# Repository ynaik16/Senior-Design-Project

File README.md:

# Senior-Design-Project
Custom Designed PCB capable of running Linux, that monitors the level of hazardous gases in the immediate environment.

This is my Senior Design Project developed by a team of 3 at California State University, East Bay. It is based on Olimex's "OLINUXINO" Linux based PCB.

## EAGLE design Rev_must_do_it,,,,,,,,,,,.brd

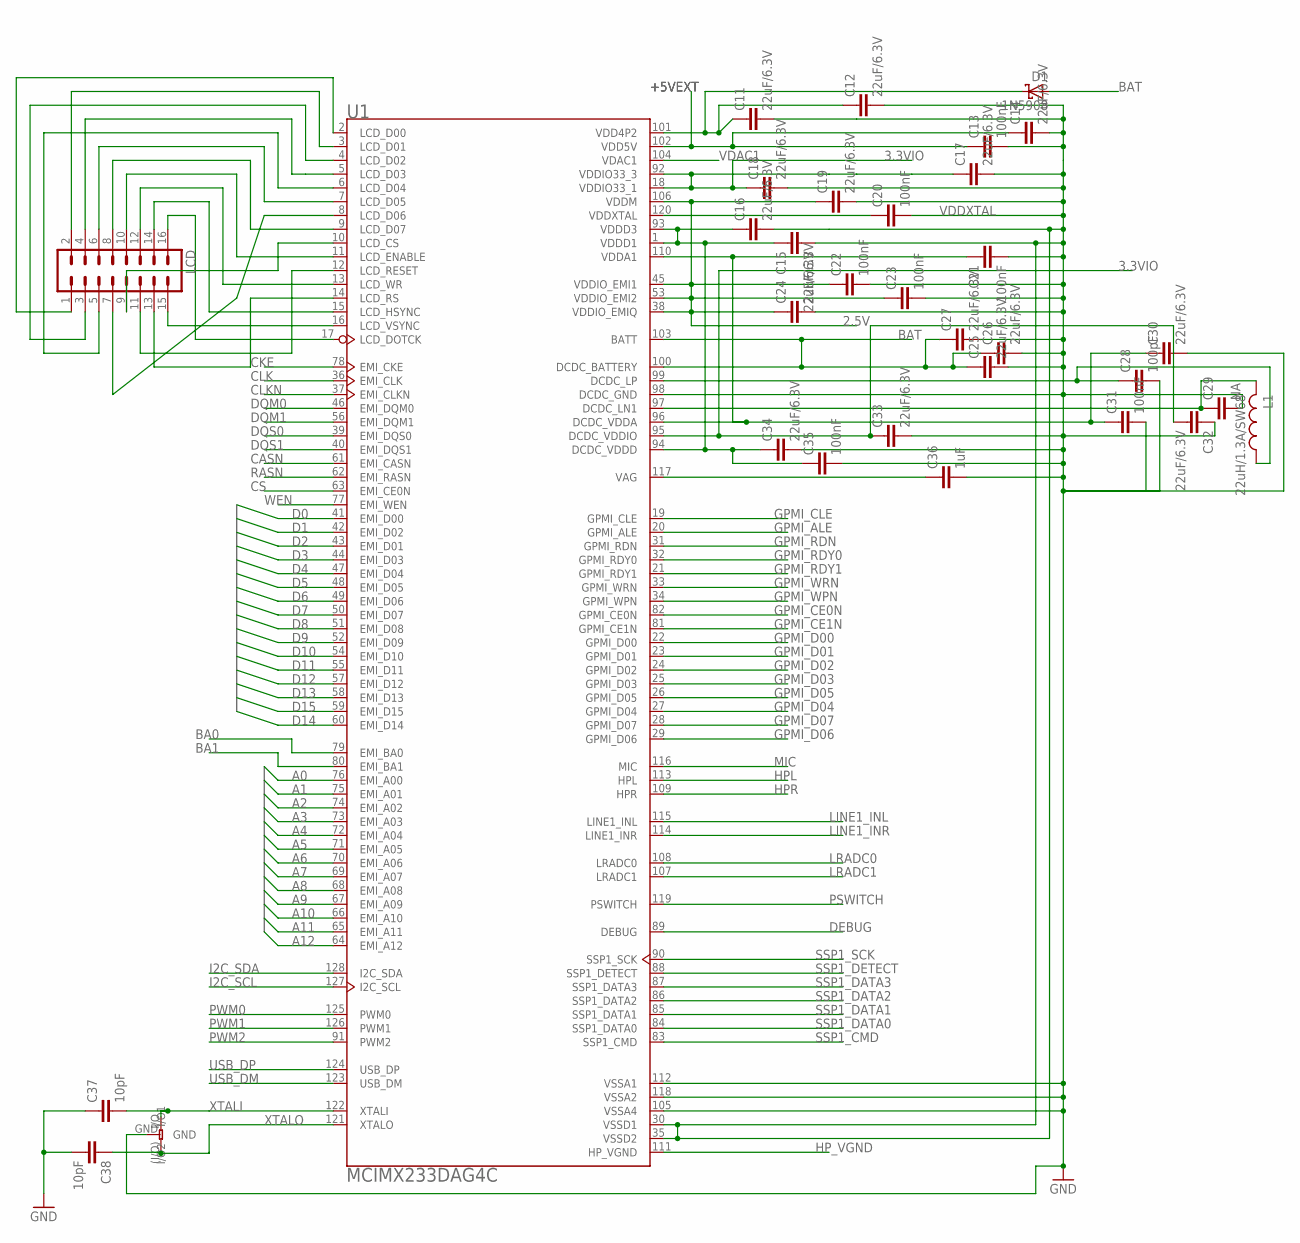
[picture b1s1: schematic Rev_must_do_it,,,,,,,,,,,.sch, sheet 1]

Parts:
C11, C12, C14, C15, C16, C17, C18, C19, C24, C25, C26, C27, C30, C32, C33, C34: 22uF/6.3V; C1206
C13, C20, C21, C22, C23, C31, C35: 100nF; C1206
C28: 100pF; C1206
C29: NA; C1206
C36: 1uF; C1206
C37, C38: 10pF; C1206
D1: 1N5908; C4111-15
L1: 22uH/1.3A/SW68; LAL02
LCD: MA08-2
U1: MCIMX233DAG4C; QFP40P1600X1600X160-128N
U$2: CRYSTAL

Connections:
2.5V: C19.1, C22.1, C23.1, C24.1, U1.38 (VDDIO_EMIQ), U1.45 (VDDIO_EMI1), U1.53 (VDDIO_EMI2), U1.106 (VDDM); also elsewhere on the board
3.3VIO: C17.1, C18.1, C32.2, C33.1, U1.18 (VDDIO33_1), U1.92 (VDDIO33_3), U1.95 (DCDC_VDDIO); also elsewhere on the board
+5VEXT: C13.1, C14.1, U1.102 (VDD5V); also elsewhere on the board
A0: U1.76 (EMI_A00); also elsewhere on the board
A1: U1.75 (EMI_A01); also elsewhere on the board
A2: U1.74 (EMI_A02); also elsewhere on the board
A3: U1.73 (EMI_A03); also elsewhere on the board
A4: U1.72 (EMI_A04); also elsewhere on the board
A5: U1.71 (EMI_A05); also elsewhere on the board
A6: U1.70 (EMI_A06); also elsewhere on the board
A7: U1.69 (EMI_A07); also elsewhere on the board
A8: U1.68 (EMI_A08); also elsewhere on the board
A9: U1.67 (EMI_A09); also elsewhere on the board
A10: U1.66 (EMI_A10); also elsewhere on the board
A11: U1.65 (EMI_A11); also elsewhere on the board
A12: U1.64 (EMI_A12); also elsewhere on the board
BA0: U1.79 (EMI_BA0); also elsewhere on the board
BA1: U1.80 (EMI_BA1); also elsewhere on the board
BAT: C25.1, C26.1, C27.1, D1.A, U1.100 (DCDC_BATTERY), U1.103 (BATT)
CASN: U1.61 (EMI_CASN); also elsewhere on the board
CKE: U1.78 (EMI_CKE); also elsewhere on the board
CLK: U1.36 (EMI_CLK); also elsewhere on the board
CLKN: U1.37 (EMI_CLKN); also elsewhere on the board
CS: U1.63 (EMI_CE0N); also elsewhere on the board
D0: U1.41 (EMI_D00); also elsewhere on the board
D1: U1.42 (EMI_D02); also elsewhere on the board
D2: U1.43 (EMI_D01); also elsewhere on the board
D3: U1.44 (EMI_D03); also elsewhere on the board
D4: U1.47 (EMI_D04); also elsewhere on the board
D5: U1.48 (EMI_D05); also elsewhere on the board
D6: U1.49 (EMI_D06); also elsewhere on the board
D7: U1.50 (EMI_D07); also elsewhere on the board
D8: U1.51 (EMI_D08); also elsewhere on the board
D9: U1.52 (EMI_D09); also elsewhere on the board
D10: U1.54 (EMI_D10); also elsewhere on the board
D11: U1.55 (EMI_D11); also elsewhere on the board
D12: U1.57 (EMI_D12); also elsewhere on the board
D13: U1.58 (EMI_D13); also elsewhere on the board
D14: U1.60 (EMI_D14)
D15: U1.59 (EMI_D15); also elsewhere on the board
DCDC_VDDA1: C21.1, C30.1, C31.1, U1.96 (DCDC_VDDA), U1.110 (VDDA1)
DCDC_VDDD: C15.1, C16.1, C34.1, C35.1, U1.1 (VDDD1), U1.93 (VDDD3), U1.94 (DCDC_VDDD)
DEBUG: U1.89 (DEBUG); also elsewhere on the board
DQM0: U1.46 (EMI_DQM0); also elsewhere on the board
DQM1: U1.56 (EMI_DQM1); also elsewhere on the board
DQS0: U1.39 (EMI_DQS0); also elsewhere on the board
DQS1: U1.40 (EMI_DQS1); also elsewhere on the board
GND: C11.2, C12.2, C13.2, C14.2, C15.2, C16.2, C17.2, C18.2, C19.2, C20.2, C21.2, C22.2, C23.2, C24.2, C25.2, C26.2, C27.2, C28.2, C29.2, C30.2, C31.2, C32.1, C33.2, C34.2, C35.2, C36.2, C37.1, C38.2, U1.30 (VSSD1), U1.35 (VSSD2), U1.98 (DCDC_GND), U1.105 (VSSA4), U1.112 (VSSA1), U1.118 (VSSA2), U$2.GND; also elsewhere on the board
GPMI_ALE: U1.20 (GPMI_ALE); also elsewhere on the board
GPMI_CE0N: U1.82 (GPMI_CE0N); also elsewhere on the board
GPMI_CE1N: U1.81 (GPMI_CE1N); also elsewhere on the board
GPMI_CLE: U1.19 (GPMI_CLE); also elsewhere on the board
GPMI_D00: U1.22 (GPMI_D00); also elsewhere on the board
GPMI_D01: U1.23 (GPMI_D01); also elsewhere on the board
GPMI_D02: U1.24 (GPMI_D02); also elsewhere on the board
GPMI_D03: U1.25 (GPMI_D03); also elsewhere on the board
GPMI_D04: U1.27 (GPMI_D04); also elsewhere on the board
GPMI_D05: U1.26 (GPMI_D05); also elsewhere on the board
GPMI_D06: U1.29 (GPMI_D06); also elsewhere on the board
GPMI_D07: U1.28 (GPMI_D07); also elsewhere on the board
GPMI_RDN: U1.31 (GPMI_RDN); also elsewhere on the board
GPMI_RDY0: U1.32 (GPMI_RDY0); also elsewhere on the board
GPMI_RDY1: U1.21 (GPMI_RDY1); also elsewhere on the board
GPMI_WPN: U1.34 (GPMI_WPN); also elsewhere on the board
GPMI_WRN: U1.33 (GPMI_WRN); also elsewhere on the board
HPL: U1.113 (HPL); also elsewhere on the board
HPR: U1.109 (HPR); also elsewhere on the board
HP_VGND: U1.111 (HP_VGND)
I2C_SCL: U1.127 (I2C_SCL); also elsewhere on the board
I2C_SDA: U1.128 (I2C_SDA); also elsewhere on the board
LINE1_INL: U1.115 (LINE1_INL); also elsewhere on the board
LINE1_INR: U1.114 (LINE1_INR); also elsewhere on the board
LRADC0: U1.108 (LRADC0); also elsewhere on the board
LRADC1: U1.107 (LRADC1); also elsewhere on the board
MIC: U1.116 (MIC); also elsewhere on the board
unnamed: C36.1, U1.117 (VAG)
unnamed: C11.1, C12.1, D1.C, U1.101 (VDD4P2)
unnamed: LCD.1, U1.2 (LCD_D00)
unnamed: C29.1, L1.2, U1.97 (DCDC_LN1)
unnamed: C28.1, L1.1, U1.99 (DCDC_LP)
unnamed: LCD.2, U1.3 (LCD_D01)
unnamed: LCD.3, U1.4 (LCD_D02)
unnamed: LCD.4, U1.5 (LCD_D03)
unnamed: LCD.5, U1.6 (LCD_D04)
unnamed: LCD.6, U1.7 (LCD_D05)
unnamed: LCD.7, U1.8 (LCD_D06)
unnamed: LCD.8, U1.9 (LCD_D07)
unnamed: LCD.9, U1.10 (LCD_CS)
unnamed: LCD.10, U1.11 (LCD_ENABLE)
unnamed: LCD.11, U1.12 (LCD_RESET)
unnamed: LCD.12, U1.13 (LCD_WR)
unnamed: LCD.13, U1.14 (LCD_RS)
unnamed: LCD.14, U1.15 (LCD_HSYNC)
unnamed: LCD.15, U1.16 (LCD_VSYNC)
unnamed: LCD.16, U1.17 (LCD_DOTCK)
PSWITCH: U1.119 (PSWITCH); also elsewhere on the board
PWM0: U1.125 (PWM0); also elsewhere on the board
PWM1: U1.126 (PWM1); also elsewhere on the board
PWM2: U1.91 (PWM2); also elsewhere on the board
RASN: U1.62 (EMI_RASN); also elsewhere on the board
SSP1_CMD: U1.83 (SSP1_CMD); also elsewhere on the board
SSP1_DATA0: U1.84 (SSP1_DATA0); also elsewhere on the board
SSP1_DATA1: U1.85 (SSP1_DATA1); also elsewhere on the board
SSP1_DATA2: U1.86 (SSP1_DATA2); also elsewhere on the board
SSP1_DATA3: U1.87 (SSP1_DATA3); also elsewhere on the board
SSP1_DETECT: U1.88 (SSP1_DETECT); also elsewhere on the board
SSP1_SCK: U1.90 (SSP1_SCK); also elsewhere on the board
USB_DM: U1.123 (USB_DM); also elsewhere on the board
USB_DP: U1.124 (USB_DP); also elsewhere on the board
VDAC1: U1.104 (VDAC1)
VDDXTAL: C20.1, U1.120 (VDDXTAL); also elsewhere on the board
WEN: U1.77 (EMI_WEN); also elsewhere on the board
XTALI: C37.2, U1.122 (XTALI), U$2.I/O (I/O2); also elsewhere on the board
XTALO: C38.1, U1.121 (XTALO), U$2.(I/O) (I/O1); also elsewhere on the board

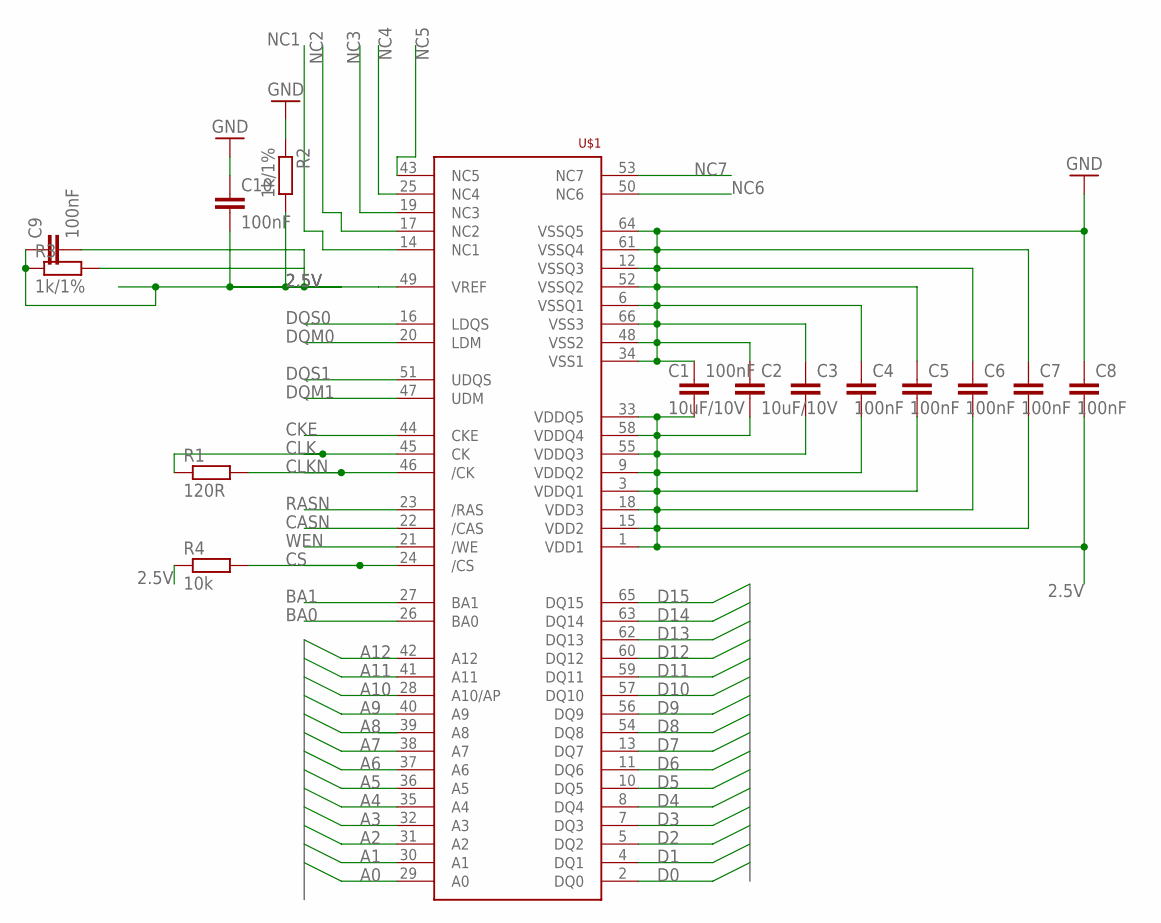
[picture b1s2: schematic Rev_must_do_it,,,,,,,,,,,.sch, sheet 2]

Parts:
C1, C3: 10uF/10V; C1206
C2, C4, C5, C6, C7, C8, C9, C10: 100nF; C1206
R1: 120R; R1206
R2, R3: 1k/1%; R1206
R4: 10k; R1206
U$1: HY5DU121622D(L)T(P)-JTSOP-II; TSOP66

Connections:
2.5V: C1.2, C2.2, C3.2, C4.2, C5.2, C6.2, C7.2, C8.2, C9.1, C9.2, C10.2, R2.2, R3.1, R4.1, U$1.1 (VDD1), U$1.3 (VDDQ1), U$1.9 (VDDQ2), U$1.15 (VDD2), U$1.18 (VDD3), U$1.33 (VDDQ5), U$1.49 (VREF), U$1.55 (VDDQ3), U$1.58 (VDDQ4); also elsewhere on the board
A0: U$1.29 (A0); also elsewhere on the board
A1: U$1.30 (A1); also elsewhere on the board
A2: U$1.31 (A2); also elsewhere on the board
A3: U$1.32 (A3); also elsewhere on the board
A4: U$1.35 (A4); also elsewhere on the board
A5: U$1.36 (A5); also elsewhere on the board
A6: U$1.37 (A6); also elsewhere on the board
A7: U$1.38 (A7); also elsewhere on the board
A8: U$1.39 (A8); also elsewhere on the board
A9: U$1.40 (A9), U$1.63 (DQ14); also elsewhere on the board
A10: U$1.28 (A10/AP); also elsewhere on the board
A11: U$1.41 (A11); also elsewhere on the board
A12: U$1.42 (A12); also elsewhere on the board
BA0: U$1.26 (BA0); also elsewhere on the board
BA1: U$1.27 (BA1); also elsewhere on the board
CASN: U$1.22 (/CAS); also elsewhere on the board
CKE: U$1.44 (CKE); also elsewhere on the board
CLK: R1.1, U$1.45 (CK); also elsewhere on the board
CLKN: R1.2, U$1.46 (/CK); also elsewhere on the board
CS: R4.2, U$1.24 (/CS); also elsewhere on the board
D0: U$1.2 (DQ0); also elsewhere on the board
D1: U$1.4 (DQ1); also elsewhere on the board
D2: U$1.5 (DQ2); also elsewhere on the board
D3: U$1.7 (DQ3); also elsewhere on the board
D4: U$1.8 (DQ4); also elsewhere on the board
D5: U$1.10 (DQ5); also elsewhere on the board
D6: U$1.11 (DQ6); also elsewhere on the board
D7: U$1.13 (DQ7); also elsewhere on the board
D8: U$1.54 (DQ8); also elsewhere on the board
D9: U$1.56 (DQ9); also elsewhere on the board
D10: U$1.57 (DQ10); also elsewhere on the board
D11: U$1.59 (DQ11); also elsewhere on the board
D12: U$1.60 (DQ12); also elsewhere on the board
D13: U$1.62 (DQ13); also elsewhere on the board
D15: U$1.65 (DQ15); also elsewhere on the board
DQM0: U$1.20 (LDM); also elsewhere on the board
DQM1: U$1.47 (UDM); also elsewhere on the board
DQS0: U$1.16 (LDQS); also elsewhere on the board
DQS1: U$1.51 (UDQS); also elsewhere on the board
GND: C1.1, C2.1, C3.1, C4.1, C5.1, C6.1, C7.1, C8.1, C10.1, R2.1, U$1.6 (VSSQ1), U$1.12 (VSSQ3), U$1.34 (VSS1), U$1.48 (VSS2), U$1.52 (VSSQ2), U$1.61 (VSSQ4), U$1.64 (VSSQ5), U$1.66 (VSS3); also elsewhere on the board
NC1: U$1.14 (NC1); also elsewhere on the board
NC2: U$1.17 (NC2); also elsewhere on the board
NC3: U$1.19 (NC3); also elsewhere on the board
NC4: U$1.25 (NC4); also elsewhere on the board
NC5: U$1.43 (NC5); also elsewhere on the board
NC6: U$1.50 (NC6); also elsewhere on the board
NC7: U$1.53 (NC7); also elsewhere on the board
RASN: U$1.23 (/RAS); also elsewhere on the board
WEN: U$1.21 (/WE); also elsewhere on the board

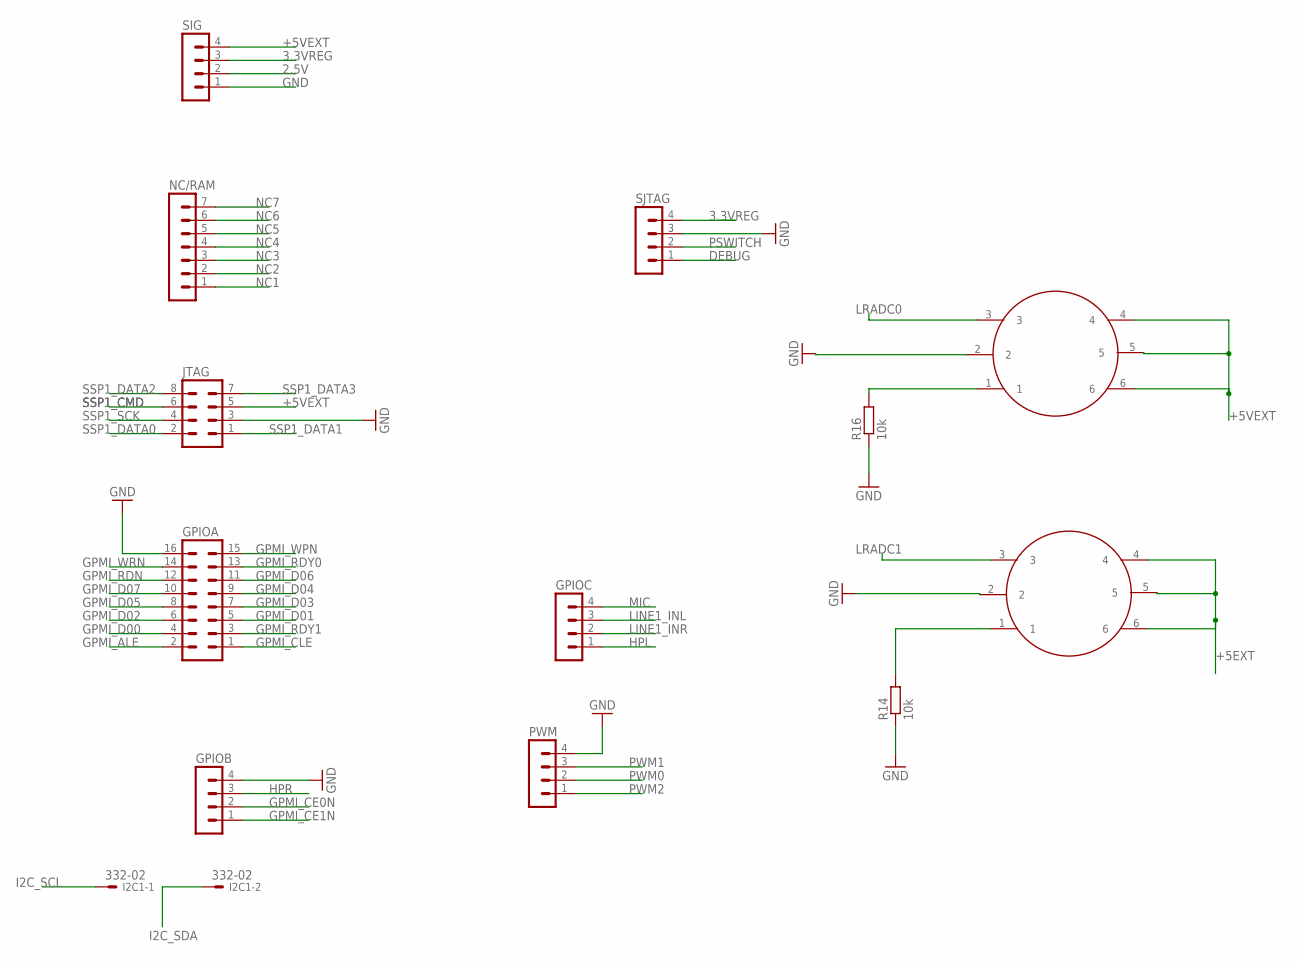
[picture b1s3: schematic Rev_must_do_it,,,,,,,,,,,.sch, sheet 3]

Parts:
GPIOA: MA08-2
GPIOB: MA04-1
GPIOC: MA04-1
I2C1: 332-02
JTAG: MA04-2
NC/RAM: MA07-1
PWM: MA04-1
R14, R16: 10k; R1206
SIG: MA04-1
SJTAG: MA04-1
U$5, U$6: SENSOR

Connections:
2.5V: SIG.2; also elsewhere on the board
3.3VREG: SIG.3, SJTAG.4; also elsewhere on the board
+5EXT: U$6.4, U$6.5, U$6.6
+5VEXT: JTAG.5, SIG.4, U$5.4, U$5.5, U$5.6; also elsewhere on the board
DEBUG: SJTAG.1; also elsewhere on the board
GND: GPIOA.16, GPIOB.4, JTAG.3, PWM.4, R14.1, R16.1, SIG.1, SJTAG.3, U$5.2, U$6.2; also elsewhere on the board
GPMI_ALE: GPIOA.2; also elsewhere on the board
GPMI_CE0N: GPIOB.2; also elsewhere on the board
GPMI_CE1N: GPIOB.1; also elsewhere on the board
GPMI_CLE: GPIOA.1; also elsewhere on the board
GPMI_D00: GPIOA.4; also elsewhere on the board
GPMI_D01: GPIOA.5; also elsewhere on the board
GPMI_D02: GPIOA.6; also elsewhere on the board
GPMI_D03: GPIOA.7; also elsewhere on the board
GPMI_D04: GPIOA.9; also elsewhere on the board
GPMI_D05: GPIOA.8; also elsewhere on the board
GPMI_D06: GPIOA.11; also elsewhere on the board
GPMI_D07: GPIOA.10; also elsewhere on the board
GPMI_RDN: GPIOA.12; also elsewhere on the board
GPMI_RDY0: GPIOA.13; also elsewhere on the board
GPMI_RDY1: GPIOA.3; also elsewhere on the board
GPMI_WPN: GPIOA.15; also elsewhere on the board
GPMI_WRN: GPIOA.14; also elsewhere on the board
HPL: GPIOC.1; also elsewhere on the board
HPR: GPIOB.3; also elsewhere on the board
I2C_SCL: I2C1.1; also elsewhere on the board
I2C_SDA: I2C1.2; also elsewhere on the board
LINE1_INL: GPIOC.3; also elsewhere on the board
LINE1_INR: GPIOC.2; also elsewhere on the board
LRADC0: U$5.3; also elsewhere on the board
LRADC1: U$6.3; also elsewhere on the board
MIC: GPIOC.4; also elsewhere on the board
unnamed: R16.2, U$5.1
unnamed: R14.2, U$6.1
NC1: NC/RAM.1; also elsewhere on the board
NC2: NC/RAM.2; also elsewhere on the board
NC3: NC/RAM.3; also elsewhere on the board
NC4: NC/RAM.4; also elsewhere on the board
NC5: NC/RAM.5; also elsewhere on the board
NC6: NC/RAM.6; also elsewhere on the board
NC7: NC/RAM.7; also elsewhere on the board
PSWITCH: SJTAG.2; also elsewhere on the board
PWM0: PWM.2; also elsewhere on the board
PWM1: PWM.3; also elsewhere on the board
PWM2: PWM.1; also elsewhere on the board
SSP1_CMD: JTAG.6; also elsewhere on the board
SSP1_DATA0: JTAG.2; also elsewhere on the board
SSP1_DATA1: JTAG.1; also elsewhere on the board
SSP1_DATA2: JTAG.8; also elsewhere on the board
SSP1_DATA3: JTAG.7; also elsewhere on the board
SSP1_SCK: JTAG.4; also elsewhere on the board

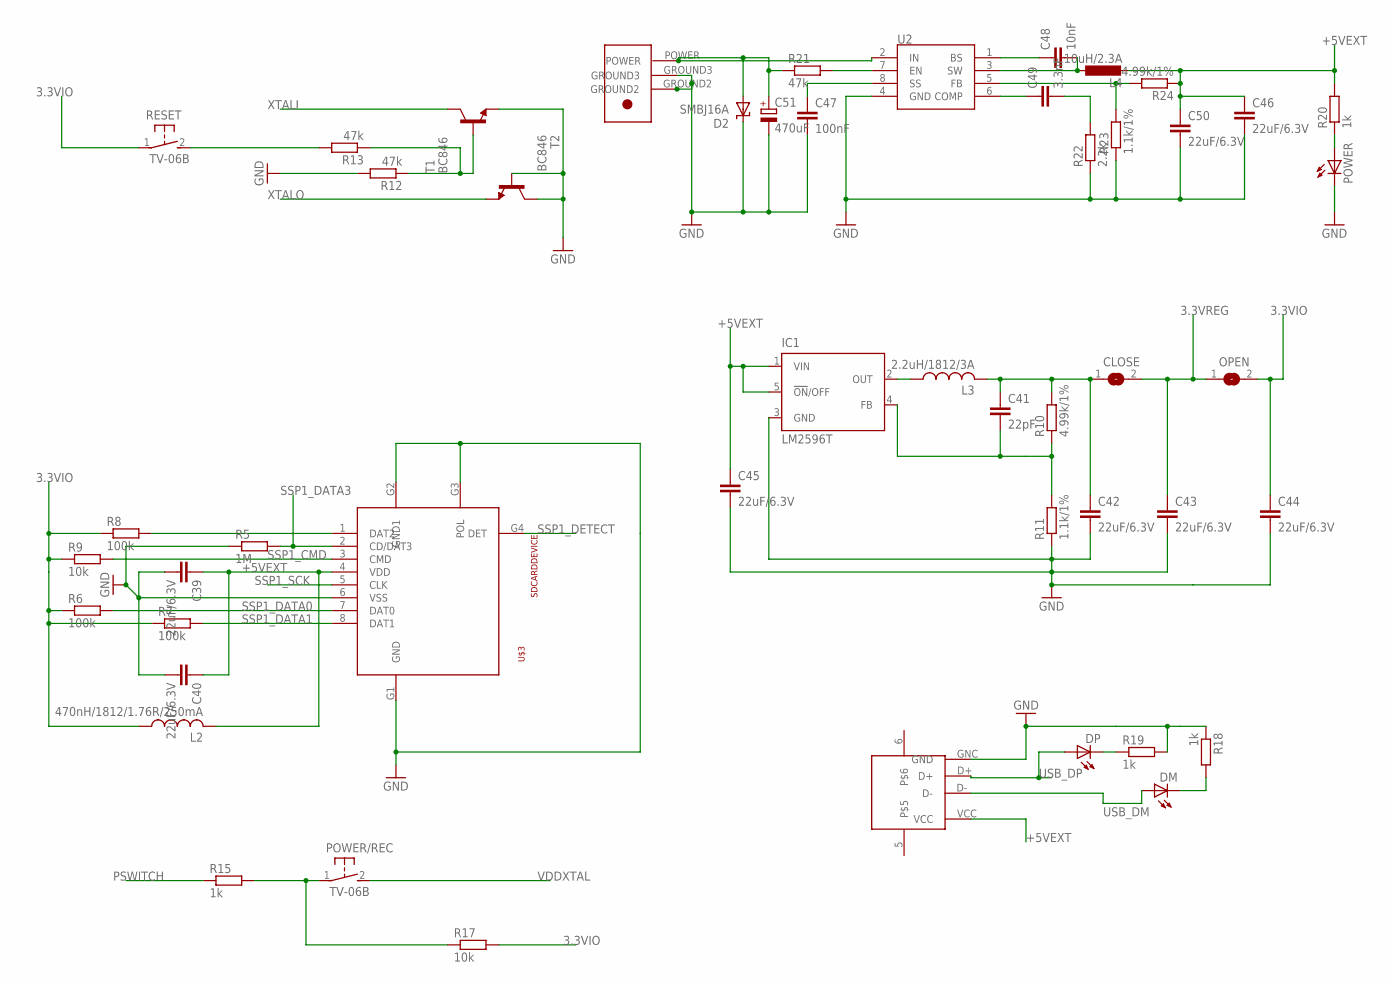
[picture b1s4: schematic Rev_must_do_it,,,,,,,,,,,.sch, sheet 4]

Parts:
C39, C40, C42, C43, C44, C45, C46, C50: 22uF/6.3V; C1206
C41: 22pF; C1206
C47: 100nF; C1206
C48: 10nF; C1206
C49: 3.3nF; C1206
C51: 470uF; 085CS_1AR
CLOSE: SJ
D2: SMBJ16A; SMBJ
DM: LED_E; LED_1206
DP: LED_E; LED_1206
IC1: LM2596T; T05D
L2: 470nH/1812/1.76R/250mA; L1812
L3: 2.2uH/1812/3A; L1812
L4: 10uH/2.3A; L1812
OPEN: SJ
POWER: LED_E; LED_1206
POWER/REC: TV-06B; B3F-31XX
R5: 1M; M1206
R6, R7, R8: 100k; M1206
R9, R17: 10k; M1206
R10: 4.99k/1%; R1206
R11: 1.1k/1%; R1206
R12, R13: 47k; R1206
R15: 1k; M1206
R18, R19, R20: 1k; R1206
R21: 47k; M0805
R22: 2.2k; M0805
R23: 1.1k/1%; M0805
R24: 4.99k/1%; M0805
RESET: TV-06B; B3F-31XX
T1, T2: BC846; SOT23
U2: MP1482; SOIC8
U$3: SDCARDDEVICE; SDCARD
U$4: USB2.0
U$7: DC_POWER

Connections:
3.3VIO: C44.1, L2.1, OPEN.2, R6.1, R7.1, R8.1, R9.1, R17.2, RESET.1; also elsewhere on the board
3.3VREG: C43.1, CLOSE.2, OPEN.1; also elsewhere on the board
+5VEXT: C39.1, C40.1, C45.1, C46.1, C50.1, IC1.1 (VIN), IC1.5 (!ON!/OFF), L2.2, L4.2, R20.2, R24.1, U$3.4 (VDD), U$4.VCC; also elsewhere on the board
GND: C39.2, C40.2, C42.2, C43.2, C44.2, C45.2, C46.2, C47.2, C50.2, C51.-, D2.C, IC1.3 (GND), POWER.C, R5.1, R11.1, R12.2, R18.1, R19.2, R22.1, R23.1, T1.2 (E), T2.1 (B), T2.3 (C), U2.4 (GND), U$3.6 (VSS), U$3.G1 (GND), U$3.G2 (GND1), U$3.G3 (POL), U$4.GNC (GND), U$7.GROUND2, U$7.GROUND3; also elsewhere on the board
unnamed: IC1.2 (OUT), L3.1
unnamed: C41.1, C42.1, CLOSE.1, L3.2, R10.2
unnamed: DP.C, R19.1
unnamed: C51.+, D2.A, R21.1, U2.2 (IN), U$7.POWER
unnamed: C41.2, IC1.4 (FB), R10.1, R11.2
unnamed: R8.2, U$3.1 (DAT2)
unnamed: POWER/REC.1, R15.2, R17.1
unnamed: R12.1, R13.1, T1.1 (B)
unnamed: R13.2, RESET.2 (S)
unnamed: DM.C, R18.2
unnamed: R21.2, U2.7 (EN)
unnamed: POWER.A, R20.1
unnamed: C47.1, U2.8 (SS)
unnamed: C48.1, U2.1 (BS)
unnamed: C48.2, L4.1, U2.3 (SW)
unnamed: C49.1, U2.6 (COMP)
unnamed: C49.2, R22.2
unnamed: R23.2, R24.2, U2.5 (FB)
PSWITCH: R15.1; also elsewhere on the board
SSP1_CMD: R9.2, U$3.3 (CMD); also elsewhere on the board
SSP1_DATA0: R6.2, U$3.7 (DAT0); also elsewhere on the board
SSP1_DATA1: R7.2, U$3.8 (DAT1); also elsewhere on the board
SSP1_DATA3: R5.2, U$3.2 (CD/DAT3); also elsewhere on the board
SSP1_DETECT: U$3.G4 (DET); also elsewhere on the board
SSP1_SCK: U$3.5 (CLK); also elsewhere on the board
USB_DM: DM.A, U$4.D-; also elsewhere on the board
USB_DP: DP.A, U$4.D+; also elsewhere on the board
VDDXTAL: POWER/REC.2 (S); also elsewhere on the board
XTALI: T1.3 (C); also elsewhere on the board
XTALO: T2.2 (E); also elsewhere on the board

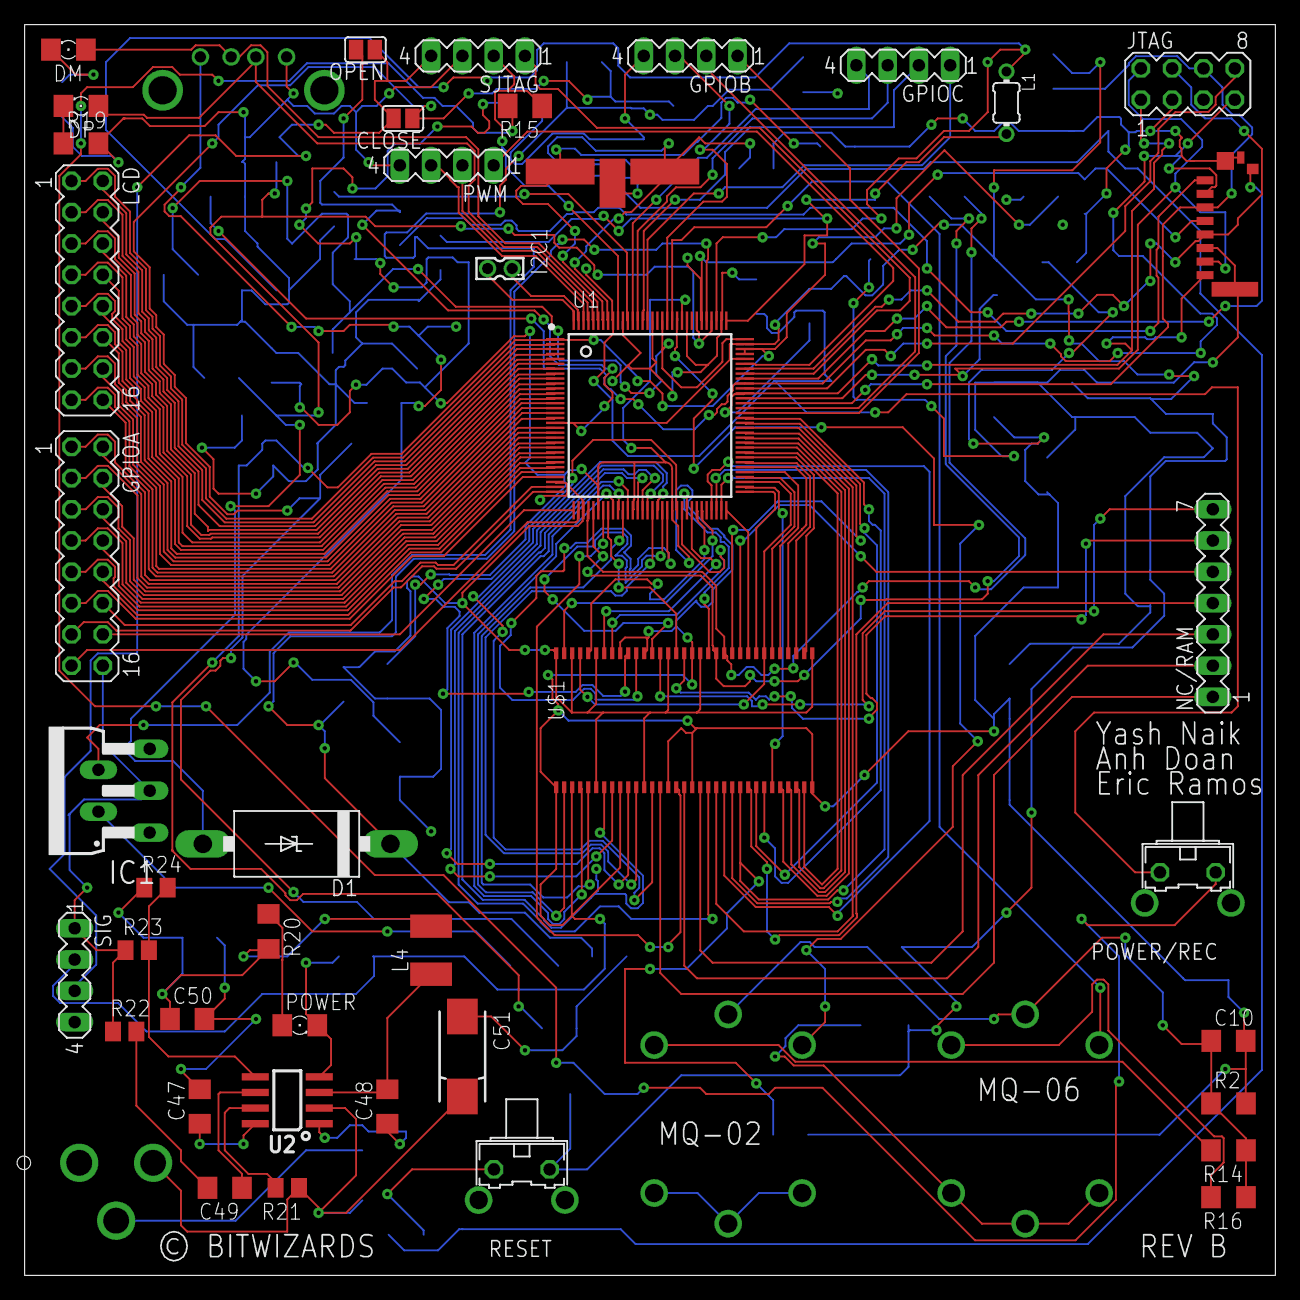
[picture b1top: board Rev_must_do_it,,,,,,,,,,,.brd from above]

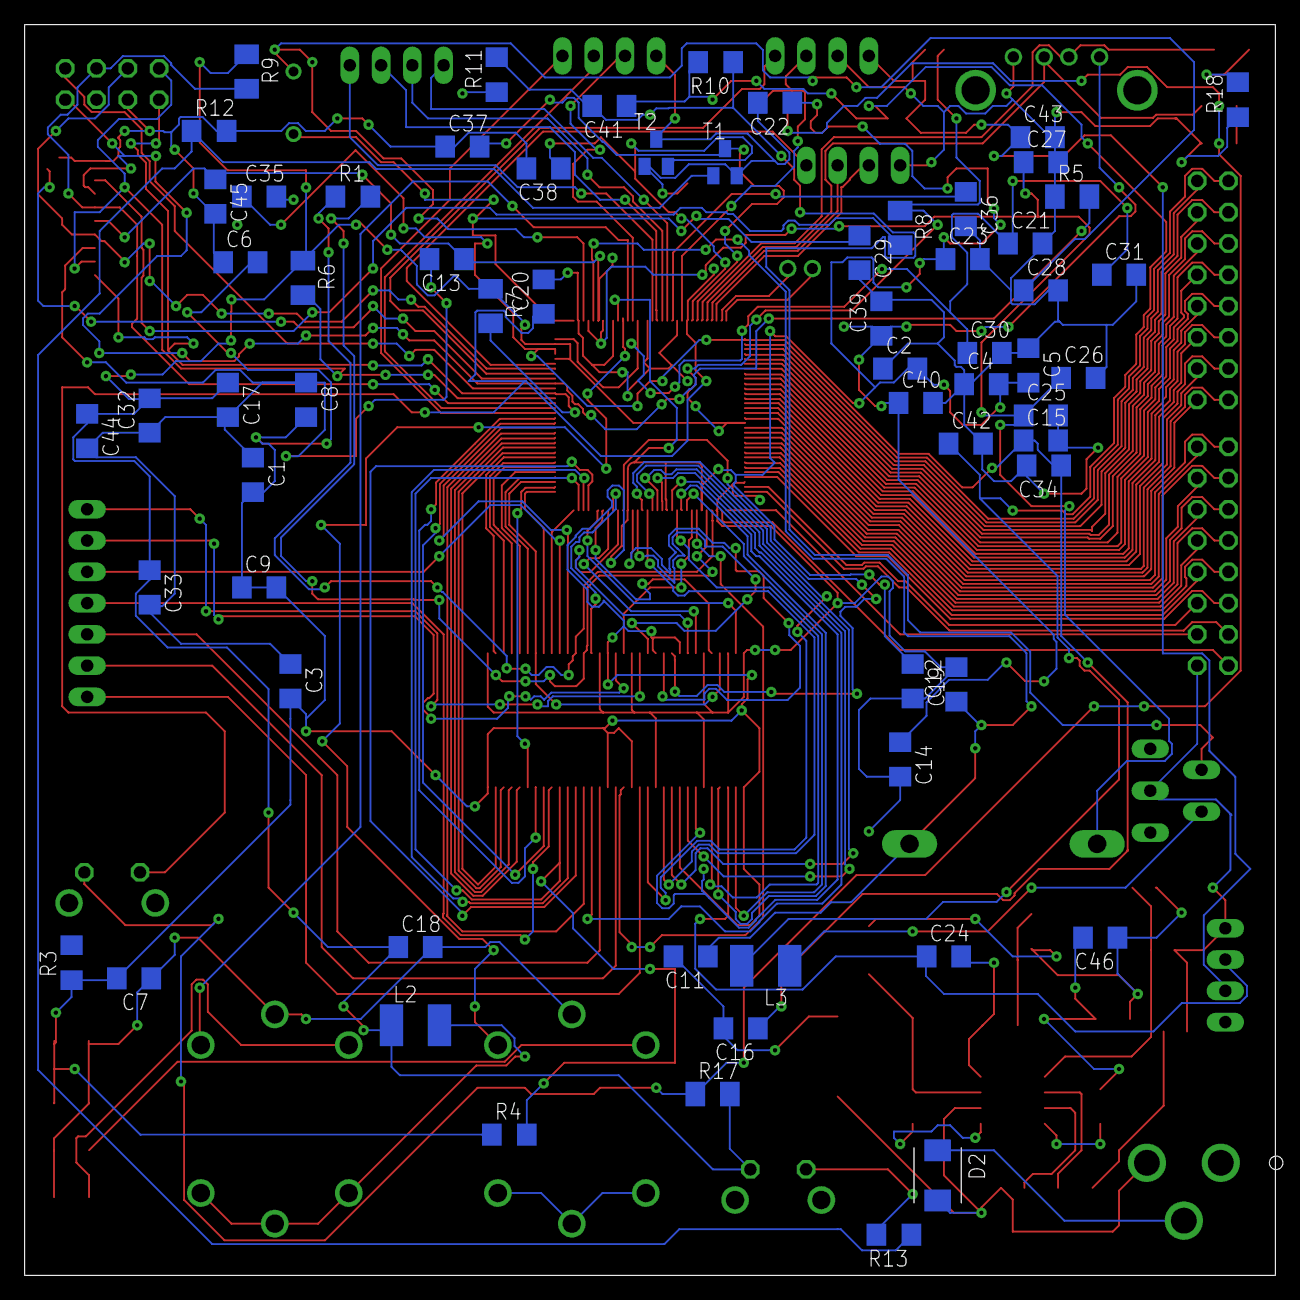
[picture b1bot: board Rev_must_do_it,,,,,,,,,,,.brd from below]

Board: 4 copper layers, 101.6 x 101.6 mm, 110 parts (64 on the bottom side), 140 nets.

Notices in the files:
Rev_must_do_it,,,,,,,,,,,.brd:
© BITWIZARDS
